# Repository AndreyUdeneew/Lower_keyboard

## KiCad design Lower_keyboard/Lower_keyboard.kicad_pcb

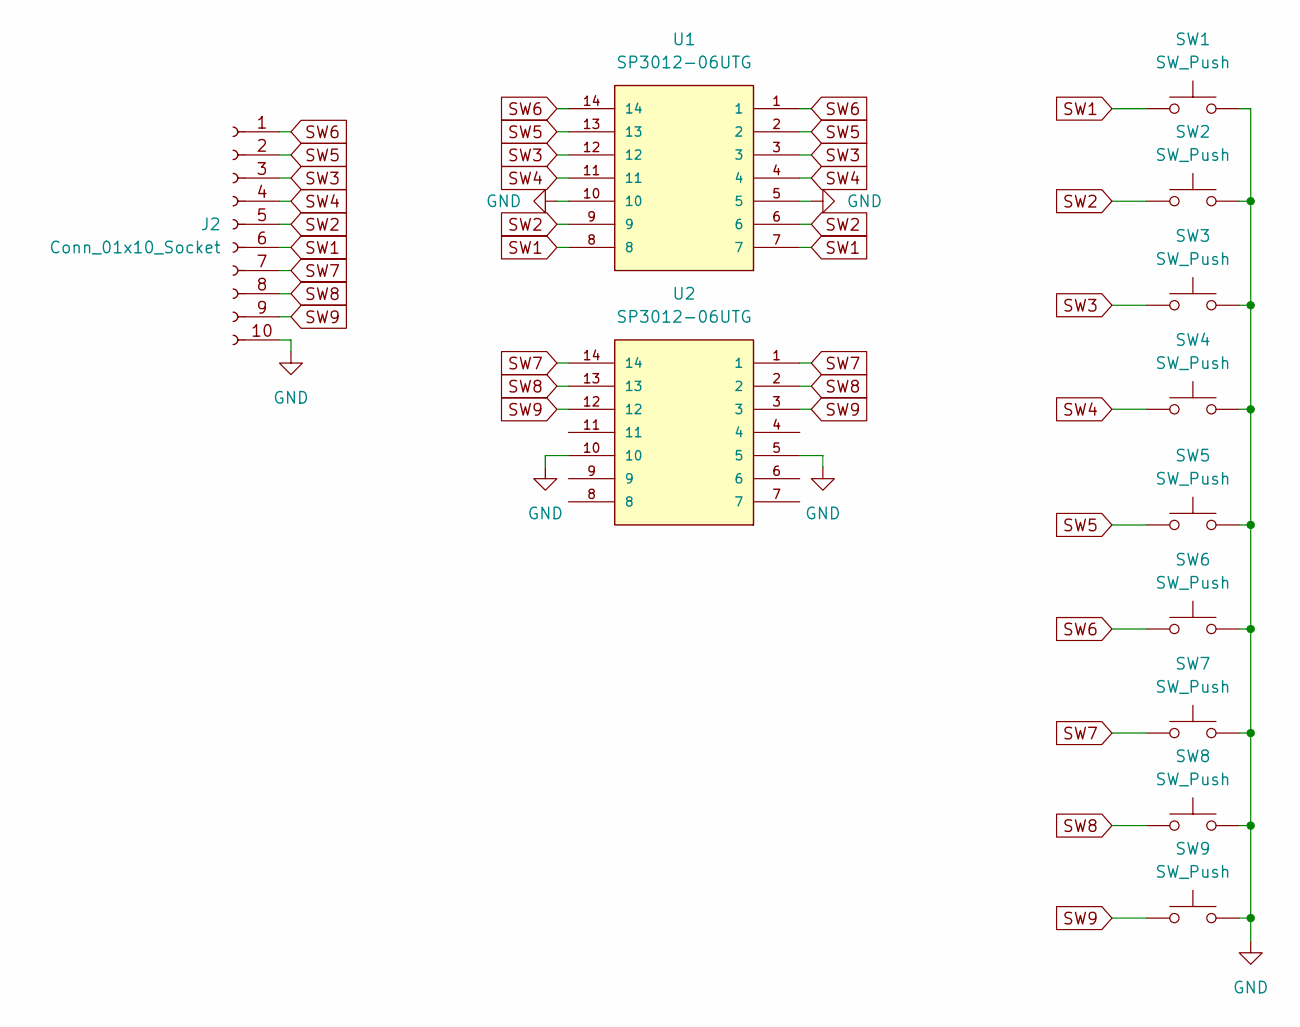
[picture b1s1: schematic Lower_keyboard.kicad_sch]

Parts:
J2: Conn_01x10_Socket; PinHeader_1x10_P1.27mm_Horizontal
SW1, SW2, SW3, SW4, SW5, SW6, SW7, SW8, SW9: SW_Push; IT-1181A
U1, U2: SP3012-06UTG; DFN-14_1.35x3.5mm_P0.5mm; PARTREV 02/23/17

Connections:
GND: J2.10, SW1.2, SW2.2, SW3.2, SW4.2, SW5.2, SW6.2, SW7.2, SW8.2, SW9.2, U1.5, U1.10, U2.5, U2.10
SW1: J2.6, SW1.1, U1.7, U1.8
SW2: J2.5, SW2.1, U1.6, U1.9
SW3: J2.3, SW3.1, U1.3, U1.12
SW4: J2.4, SW4.1, U1.4, U1.11
SW5: J2.2, SW5.1, U1.2, U1.13
SW6: J2.1, SW6.1, U1.1, U1.14
SW7: J2.7, SW7.1, U2.1, U2.14
SW8: J2.8, SW8.1, U2.2, U2.13
SW9: J2.9, SW9.1, U2.3, U2.12

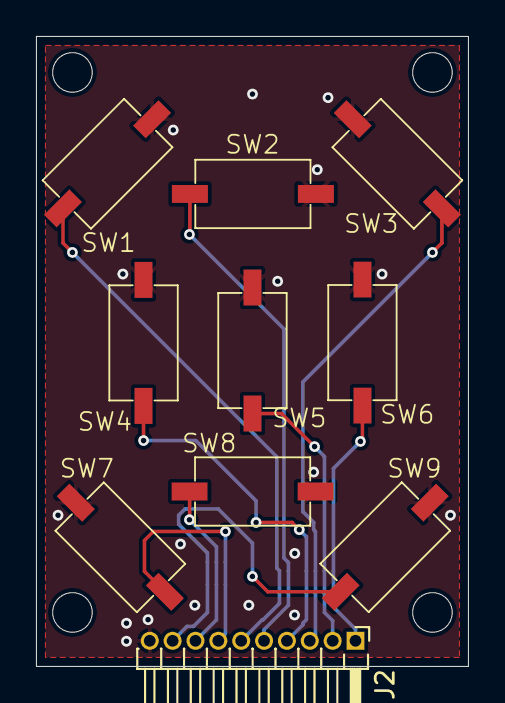
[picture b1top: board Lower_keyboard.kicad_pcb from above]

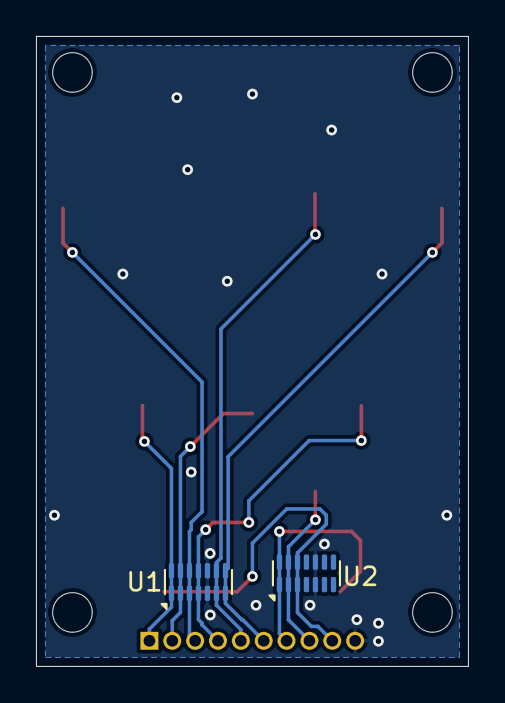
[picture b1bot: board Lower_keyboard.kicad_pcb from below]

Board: 2 copper layers, 24.0 x 35.0 mm, 12 parts (2 on the bottom side), 10 nets.

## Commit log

2025-02-12 v0.1 ordered
2025-02-12 v0.2 backup *.zip was created
